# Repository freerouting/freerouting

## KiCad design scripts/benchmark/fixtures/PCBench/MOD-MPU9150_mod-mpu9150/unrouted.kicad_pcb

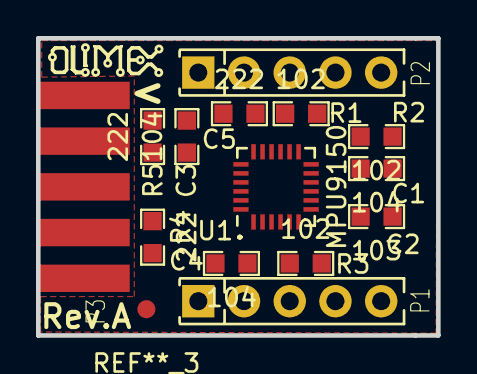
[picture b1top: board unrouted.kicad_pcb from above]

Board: 2 copper layers, 22.2 x 16.5 mm, 14 parts (0 on the bottom side), 12 nets, no tracks yet.

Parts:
C1, C3, C4: 104; C_0603
C2: 103; C_0603
C5: 222; C_0603
P1, P2: CONN_01X05; SIP5_Housing
P3: HE10-10; UEXTF
R1, R2, R3: 102; R_0603
R4, R5: 222; R_0603
U1: MPU9150; QFN-24-1EP_4x4mm_Pitch0.5mm

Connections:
/SCL: P3.5, R5.2, U1.23
/SDA: P3.6, R4.2, U1.24
AD0: P2.3, R1.1, U1.9
CLKIN: P1.3, R3.1, U1.1
GND: C1.2, C2.2, C3.2, C4.2, C5.1, P1.2, P2.2, P3.2, R1.2, R2.2, R3.2, U1.15, U1.17, U1.18
unnamed: C1.1, U1.10
unnamed: C5.2, U1.20
unnamed: P1.4, U1.6
unnamed: P1.5, U1.7
unnamed: P2.4, U1.12
unnamed: P2.5, R2.1, U1.11
VDD: C2.1, C3.1, C4.1, P1.1, P2.1, P3.1, R4.1, R5.1, U1.3, U1.8, U1.13

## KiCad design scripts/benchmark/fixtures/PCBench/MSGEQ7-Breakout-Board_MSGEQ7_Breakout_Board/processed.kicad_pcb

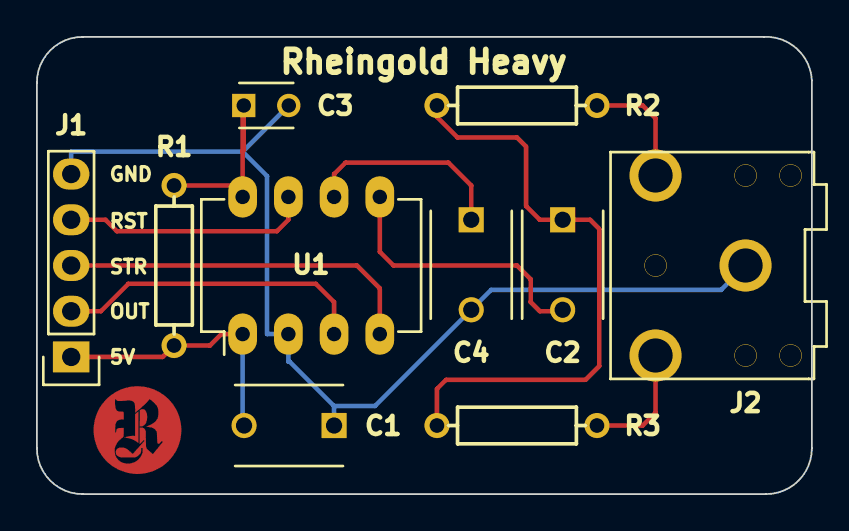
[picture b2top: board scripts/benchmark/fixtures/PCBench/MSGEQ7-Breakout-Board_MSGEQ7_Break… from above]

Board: 2 copper layers, 43.1 x 25.4 mm, 13 parts (0 on the bottom side), 11 nets.

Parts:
C1, C2, C4: 0.1uF; C_Disc_D6_P5
C3: 33pF; C_Disc_D3_P2.5
J1: BREAKOUT_BOARD_HEADER; Pin_Header_Straight_1x05
J2: STEREO_MINI_JACK; 3.5mm_Stereo_Jack_SJ1-3523NG
R1: 200K; PTH_Resistor
R2, R3: 22K; PTH_Resistor
U1: MSGEQ7; DIP-8_W7.62mm_LongPads
VAL: REF; Logo_RH_Circle_R_B.SilkS_.750in_flipped
VAL_2: REF; Logo_RH_Circle_R__F.Mask_.2in
VAL_3: REF; Logo_RH_Circle_R__F.Cu_.2in

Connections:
+5V: C1.2, J1.1, R1.2, U1.1
GND: C1.1, C3.2, C4.2, J1.5, J2.1, U1.2
unnamed: C2.1, R2.1, R3.1
unnamed: C2.2, U1.5
unnamed: C3.1, R1.1, U1.8
unnamed: C4.1, U1.6
unnamed: J2.2, R2.2
unnamed: J2.3, R3.2
OUT: J1.2, U1.3
RESET_IN: J1.4, U1.7
STROBE: J1.3, U1.4

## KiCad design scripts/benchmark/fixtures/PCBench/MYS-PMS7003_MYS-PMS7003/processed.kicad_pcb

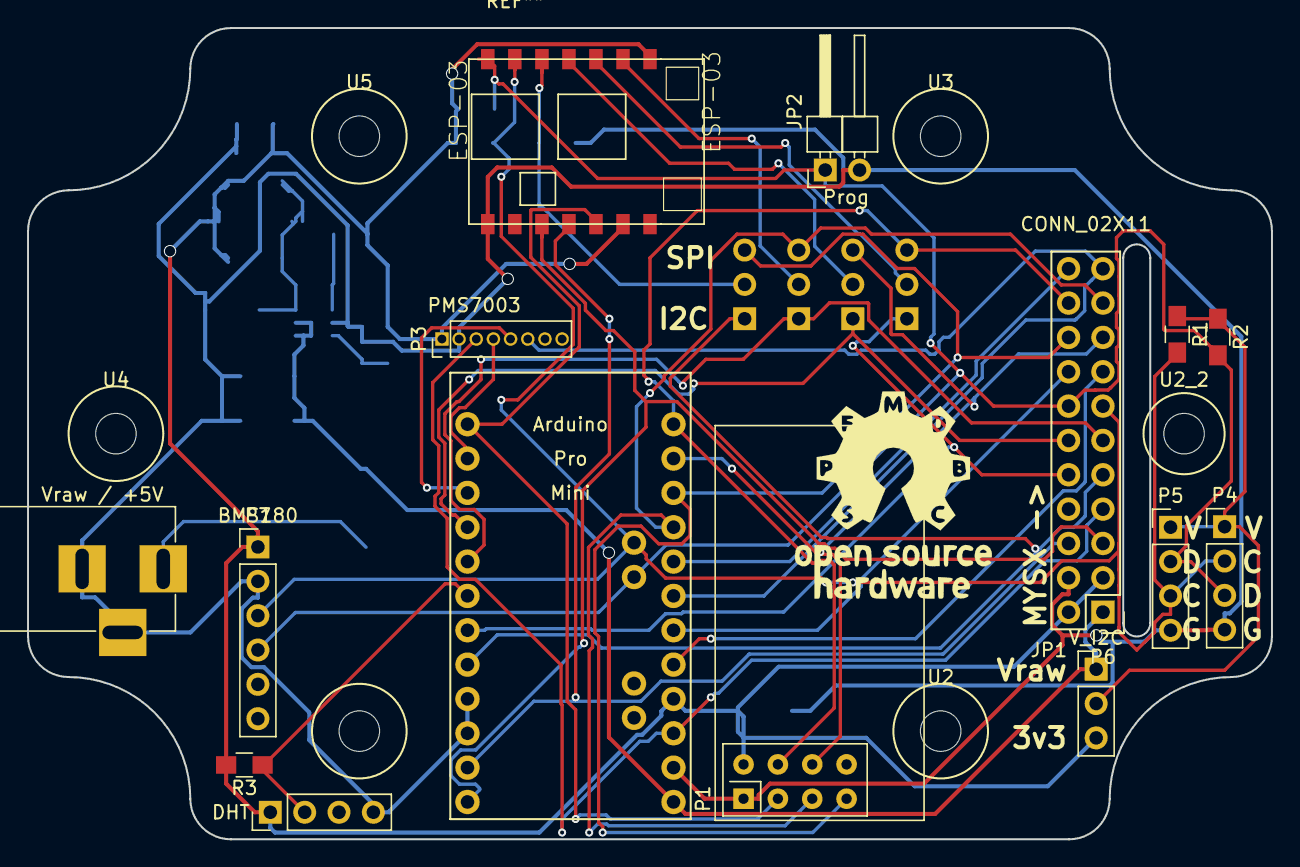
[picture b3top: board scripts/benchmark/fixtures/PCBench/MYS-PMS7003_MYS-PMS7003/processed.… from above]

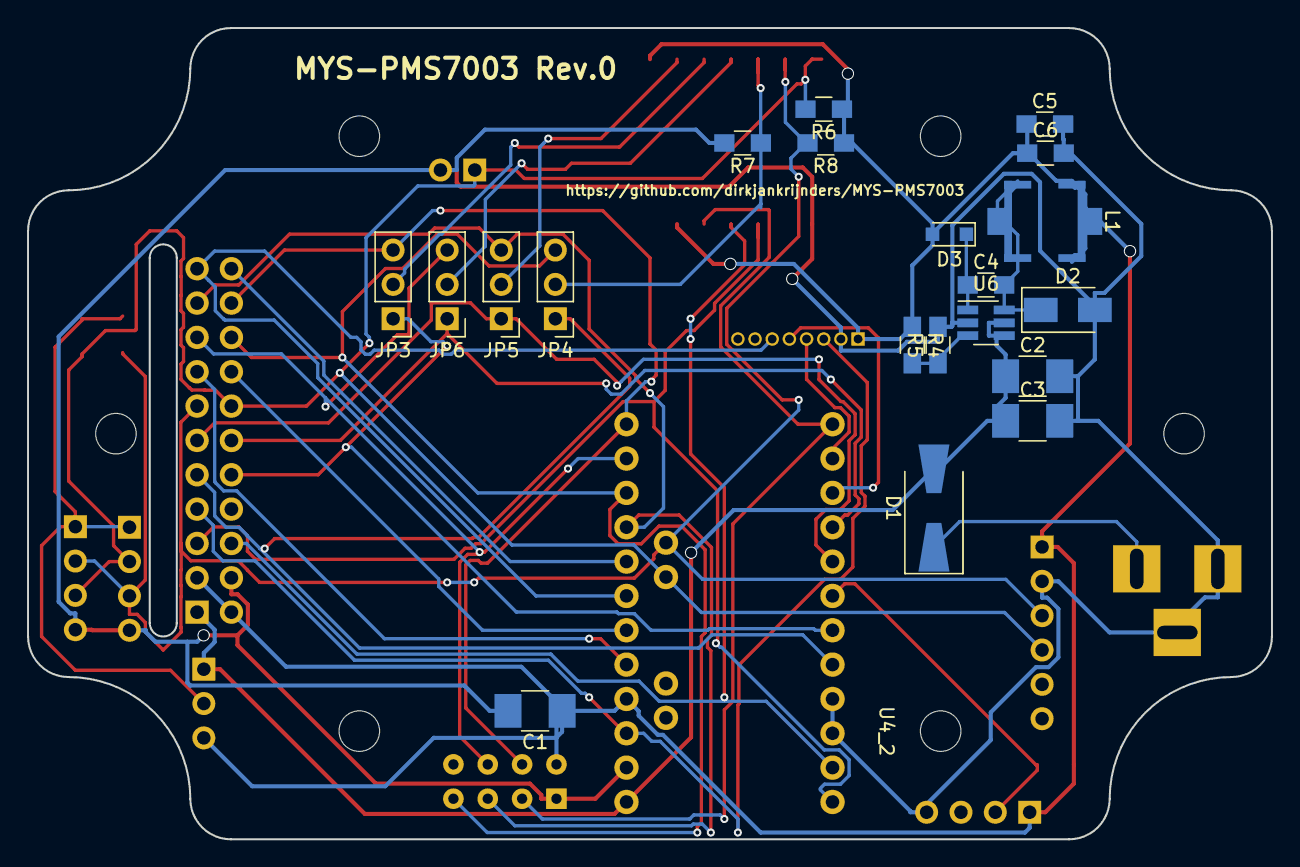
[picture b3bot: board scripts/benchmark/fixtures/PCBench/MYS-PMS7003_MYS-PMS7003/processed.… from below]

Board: 2 copper layers, 92.0 x 60.0 mm, 41 parts (21 on the bottom side), 33 nets.

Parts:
C1, C2, C3: 4u7; R_1210_HandSoldering
C4: 100 nF; R_0805_HandSoldering
C5, C6: 10u; R_0805_HandSoldering
D1: DIODE; D_SMA-SMB_Universal_Handsoldering
D2: B140; D_SMA
D3: 1N4148; D_SOD-323_HandSoldering
ESP-03: ESP-03
JP1, JP3, JP4, JP5, JP6: Jumper_NC_Dual; Pin_Header_Straight_1x03_Pitch2.54mm
JP2: Jumper; Pin_Header_Angled_1x02_Pitch2.54mm
L1: 15 μH; L_Coilcraft_MSS6132
P1: CONN_02X04; nRF24L01_Breakout
P2: CONN_01X03; Pin_Header_Straight_1x04_Pitch2.54mm
P3: CONN_01X08; Pin_Header_Straight_1x08_Pitch1.27mm
P4, P5: CONN_01X04; Pin_Header_Straight_1x04_Pitch2.54mm
P6: CONN_02X11; MYSX_2.6
P7: CONN_01X06; Pin_Header_Straight_1x06_Pitch2.54mm
R1, R2, R3: R; R_0805_HandSoldering
R4: 31k6; R_0805_HandSoldering
R5: 10k; R_0805_HandSoldering
R6, R7, R8: 12k; R_0805_HandSoldering
U1: Arduino_Pro_Micro; Arduino_Pro_Mini
U2, U2_2, U3, U4, U4_2, U5: M3_Mounting_hole; MountingHole_3mm
U6: MCP16301; SOT-23-6_Handsoldering
Vraw / +5V: BARREL_JACK

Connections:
+3V3: C1.1, C5.1, C6.1, D3.2, ESP-03.6, ESP-03.8, JP1.3, L1.2, P1.2, P2.1, P3.1, P6.2, P6.3, P7.1, R3.2, R4.1, R6.1, R8.1, U1.16
/DHT_DATA: P2.2, R3.1, U1.6
/MYSX_D1_DFM: ESP-03.3, P6.5, U1.12
/MYSX_D2_DTM: ESP-03.4, P6.6, U1.11
/MYSX_D3_INT: JP4.1, P6.9, U1.8
/MYSX_D4_INT: JP3.1, P6.10, U1.7
/MYSX_D5_PWM: JP5.1, P6.11, U1.5
/MYSX_D6_PWM: JP6.1, P6.12, U1.4
/MYSX_D7_SCL: ESP-03.13, P4.2, P5.3, P6.13, P7.3, R1.2, R8.2, U1.26
/MYSX_D8_SDA: ESP-03.14, JP2.1, P4.3, P5.2, P6.14, P7.4, R2.2, R6.2, U1.25
/MYSX_D9_A3: P6.15, U1.17
/MYSX_D10_A4: P6.16, U1.18
/MYSX_D11_MOSI: JP6.3, P1.6, P6.17, U1.23
/MYSX_D12_MISO: JP4.3, P1.7, P6.18, U1.22
/MYSX_D13_SCLK: JP5.3, P1.5, P6.19, U1.21
/MYSX_D14_CS: JP3.3, P1.4, P6.20, U1.24
/MYSX_D15_A5: P3.6, P6.21, U1.19
/MYSX_D16_A6: P6.22, U1.20
/MYSX_RST: P3.3, P6.7, U1.15
/NRF24_CE: ESP-03.5, P1.3, U1.1
/SS_RX: P3.4, U1.2
/SS_TX: P3.5, U1.3
/Vraw: C2.1, C3.1, D1.2, JP1.1, P6.1, U1.13, U6.4, U6.5
GND: C1.2, C2.2, C3.2, C5.2, C6.2, D2.2, ESP-03.1, JP2.2, P1.1, P2.4, P3.2, P4.4, P5.4, P6.4, P7.2, R5.2, R7.2, U1.9, U1.10, U1.14, U6.2, Vraw / +5V.2, Vraw / +5V.3
unnamed: C4.1, D3.1, U6.1
unnamed: C4.2, D2.1, L1.1, U6.6
unnamed: D1.1, Vraw / +5V.1
unnamed: JP1.2, P4.1, P5.1, R1.1, R2.1
unnamed: ESP-03.10, JP3.2
unnamed: ESP-03.12, JP4.2, R7.1
unnamed: ESP-03.9, JP5.2
unnamed: ESP-03.11, JP6.2
unnamed: R4.2, R5.1, U6.3

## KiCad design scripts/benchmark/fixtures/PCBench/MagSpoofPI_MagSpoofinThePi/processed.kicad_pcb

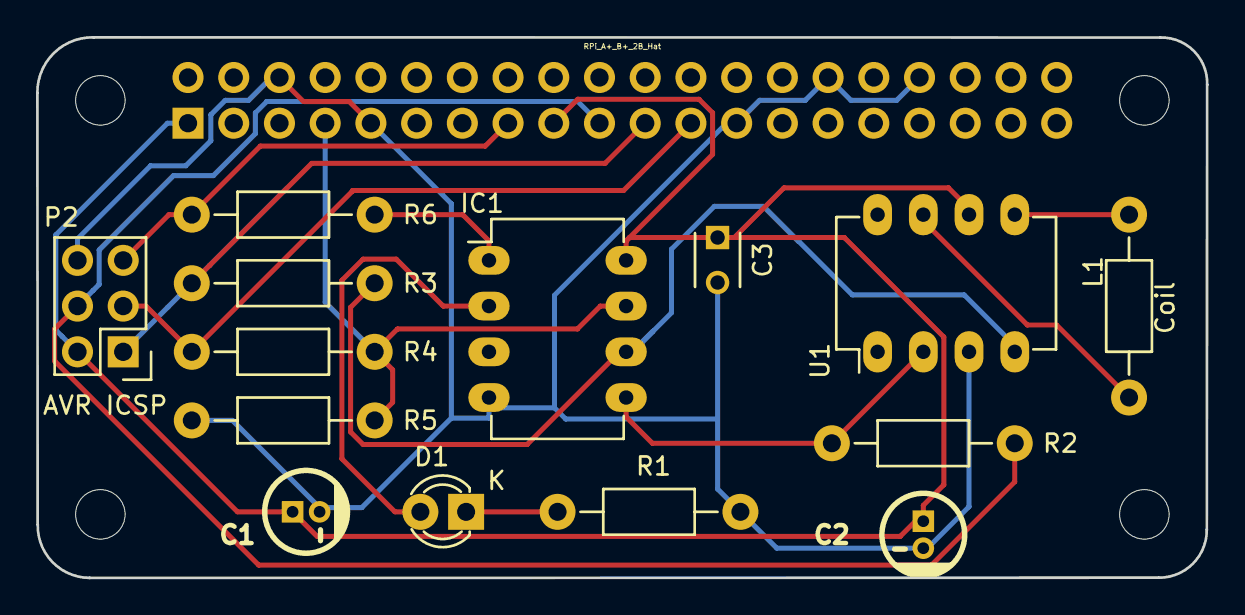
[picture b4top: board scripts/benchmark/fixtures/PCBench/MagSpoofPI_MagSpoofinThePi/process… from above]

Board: 2 copper layers, 65.0 x 30.0 mm, 16 parts (1 on the bottom side), 14 nets.

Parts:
C1, C2: 100uF; CP_4x5mm
C3: 0.1uF; C_Disc_D3_P2.5
D1: LED; LED-3MM
IC1: ATTINY85-P; DIP-8_W7.62mm_LongPads
L1: Coil; Resistor_Horizontal_RM10mm
Noname_1: OSHW-Logo; Symbol_OSHW-Logo_SilkScreen
P2: AVR ICSP; Pin_Header_Straight_2x03
R1: 330; Resistor_Horizontal_RM10mm
R2, R3, R4, R6: 1K; Resistor_Horizontal_RM10mm
R5: 10K; Resistor_Horizontal_RM10mm
U1: TC4424; DIP-8_W7.62mm_LongPads
U2: RPi_A+_B+_2B_Hat; z_RPiZero_Hat_NPTH

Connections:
/GPIO4: IC1.7, R4.2, R5.1, U2.7
/MISO: P2.1, R3.1, U2.21
/MOSI: P2.4, R2.1, U2.19
/RST: P2.5, R6.2, U2.15
/SCK: P2.3, R4.1, U2.23
GND: C1.2, C2.2, C3.2, IC1.4, P2.6, R1.2, R5.2, U1.3, U2.6, U2.9, U2.25, U2.30, U2.34
unnamed: D1.1, R1.1
unnamed: D1.2, IC1.2
unnamed: IC1.1, R6.1
unnamed: IC1.5, R2.2, U1.2
unnamed: IC1.6, R3.2, U1.4
unnamed: L1.1, U1.7
unnamed: L1.2, U1.5
VCC: C1.1, C2.1, C3.1, IC1.8, P2.2, U1.6, U2.1, U2.17
